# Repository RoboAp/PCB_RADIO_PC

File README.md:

# VSSS Communication Base - RASPBERRY PI PICO & NRF24L01 🛰️

Este repositório contém o projeto de hardware (PCB) da base emissora/receptora desenvolvida para a equipe **roboAp (UTFPR - Apucarana)**. O módulo é responsável pelo link de comunicação entre a estação de processamento (PC) e os robôs da categoria **Very Small Size Soccer (VSSS)**.

## 📋 Visão Geral

A placa atua como um dongle USB de alto desempenho. Ela utiliza o processamento do **RP2350** para gerenciar o tráfego de dados e o rádio **NRF24L01** para a transmissão em tempo real, garantindo baixa latência nos comandos de trajetória.

## 🛠 Especificações de Hardware

* **Microcontrolador:** PI PICO 2 RP2350
* **Transceptor:** NRF24L01+ (2.4 GHz)
* **Alimentação:** Barramento USB (5V)
* **Interface:** Serial-to-SPI Bridge

## 📐 Destaques do Design (Layout & RF)

O projeto foca na integridade do sinal e na redução de ruído eletromagnético (EMI), considerando o ambiente crítico de competições:

* **RF Overhang (Antena em Balanço):** O conector do NRF24L01 foi posicionado na borda da PCB com o transceptor em balanço (*overhanging*). Isso projeta a antena para fora da área da placa, eliminando a absorção de sinal pelo plano de cobre.
* **Isolamento de Camadas:** Roteamento de sinais e trilhas de alimentação realizado na camada inferior (**B.Cu**), mantendo o módulo de rádio na camada superior (**F.Cu**) para minimizar o acoplamento parasita.
* **Filtragem de Transientes:** Preparada para a inclusão de capacitores de desacoplamento (**100nF cerâmico** e **10µF eletrolítico**) próximos aos pinos de alimentação do NRF. Essencial para estabilizar os picos de corrente durante a transmissão.
* **EMC Optimization:** Firmware configurado para desativar os rádios internos do ESP32 (WiFi/Bluetooth), focando os recursos de energia e processamento exclusivamente no protocolo SPI do rádio externo.

## 📂 Estrutura do Repositório

* `/Hardware`: Arquivos de projeto da PCB (KiCad/EasyEDA), Esquema Elétrico e Gerbers.
* `/Firmware`: Código fonte para a ponte serial e configuração de baixa latência do NRF24L01.
* `/Docs`: Relatórios de testes de bancada e medições de performance.

## 🔧 Configuração e Uso

1. **Firmware:** Ao carregar o código, certifique-se de utilizar `WiFi.mode(WIFI_OFF)` para garantir a estabilidade do link de RF.
2. **Conexão:** Plugue via USB e utilize o terminal (ou software de estratégia) para enviar os comandos via porta Serial.
3. **Hardware:** Recomendado o uso de capacitores de filtro se a comunicação apresentar perda de pacotes (*Packet Loss*) em distâncias superiores a 2 metros.

## 👥 Créditos

* **Desenvolvedor:** Michel Rochytor Lima Barbosa
* **Instituição:** UTFPR - Campus Apucarana
* **Equipe:** [roboAp - Robotics Team](https://github.com/roboap)

---
Projeto desenvolvido sob licença MIT.

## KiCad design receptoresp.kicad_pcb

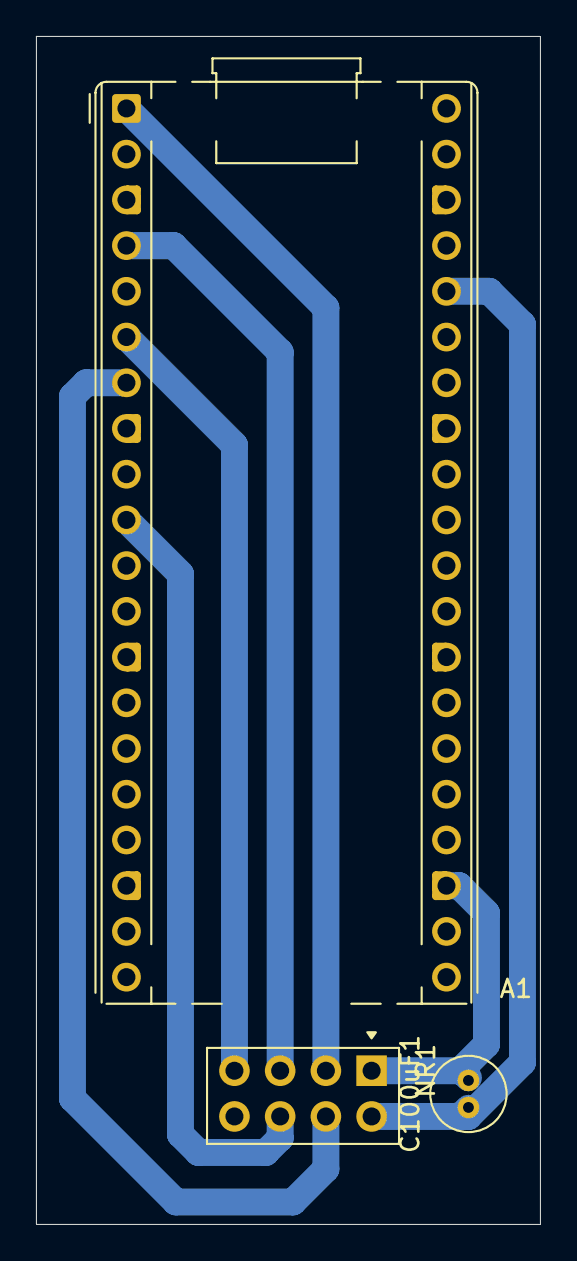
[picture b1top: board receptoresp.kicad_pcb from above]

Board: 2 copper layers, 28.0 x 66.0 mm, 3 parts (0 on the bottom side), 7 nets.

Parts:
A1: RaspberryPi_Pico; RaspberryPi_Pico_Common_THT
C100uF1: C_Polarized; C_Radial_D4.0mm_H5.0mm_P1.50mm
NR1: NRF24L01; nRF24L01_Breakout

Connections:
unnamed: A1.36 (3V3), C100uF1.1, NR1.2 (VCC)
unnamed: A1.1 (GPIO0), NR1.3 (CE)
unnamed: A1.4 (GPIO2), NR1.5 (SCK)
unnamed: A1.6 (GPIO4), NR1.7 (MIS0)
unnamed: A1.7 (GPIO5), NR1.4 (CSN)
unnamed: A1.10 (GPIO7), NR1.6 (MOSI)
unnamed: A1.3 (GND), A1.8 (GND), A1.13 (GND), A1.18 (GND), A1.23 (GND), A1.28 (GND), A1.38 (GND), C100uF1.2, NR1.1 (GND)

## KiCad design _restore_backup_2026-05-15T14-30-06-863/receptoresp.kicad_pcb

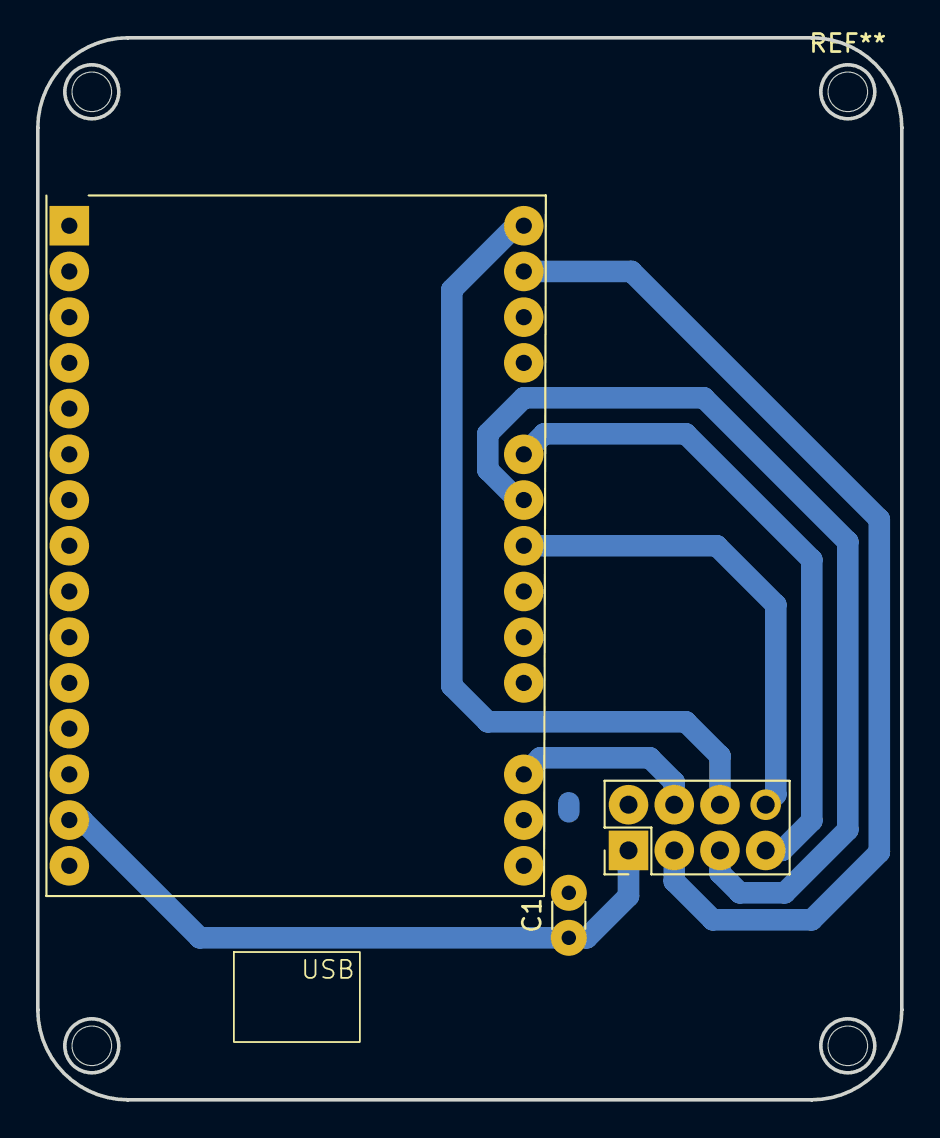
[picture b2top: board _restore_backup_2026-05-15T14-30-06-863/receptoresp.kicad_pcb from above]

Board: 2 copper layers, 48.0 x 59.0 mm, 3 parts (0 on the bottom side), 9 nets.

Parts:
C1: C; C_Disc_D3.0mm_W1.6mm_P2.50mm
E1: ESP-WROOM-32
NR1: NRF24L01

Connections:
unnamed: C1.1, E1.16 (3V3)
unnamed: E1.23 (D5), NR1.8 (IRQ)
unnamed: E1.18 (D15), NR1.4 (CSN)
unnamed: E1.24 (D18), NR1.5 (SCK)
unnamed: E1.25 (D19), NR1.7 (MIS0)
unnamed: E1.29 (D22), NR1.3 (CE)
unnamed: E1.30 (D23), NR1.6 (MOSI)
unnamed: E1.14 (GND), NR1.1 (GND)
unnamed: C1.2, NR1.2 (VCC)

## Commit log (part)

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2026-05-11 PCB sem capacitor -_-
2026-05-11 Revise README with project details and specifications
    Updated project title and added detailed project description, specifications, design highlights, repository structure, setup instructions, and credits.
2026-05-14 capacitor colocado para o modulo nrf
2026-05-16 capacitor polalizado 100uF
